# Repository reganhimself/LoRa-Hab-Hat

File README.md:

# Raspberry Zero LoRa HAB HAT
This is a Pi Hat designed to work with a Raspberry Pi. It was specifically designed to work with Raspberry Pi Zero and the mounting holes are lined up with Pi Zero in mind however it should still work with any other Pi. This board is designed to transform a Pi Zero into a tracker. On the board, you will find SMD pads to solder a LoRa module on to. The board supports the following modules: RFM95, RFM95, RFM97, RFM98. There is also an option of connecting a 6 pin GPS receiver to the board if needed as well. The breakout for Rasberry Pi provides not only pins but also pads. This gives you an ability to test with jumper wires and for use have a more permanent connection.

This board was made in collaboration with [Reganhimself](http://reganhimself.com). Tests and projects with this board will be on his forum.  

Here is a quick overview of the board:

# The top side

# Bottom side

# And here is the schematic for the board

# Our Board uses a standard Pi Zero pinout:

## BOM

| component  | Version  | Link  | Notes |
|---|---|---|---|
| Raspberry Pi Zero  | 1.3  | https://thepihut.com/products/raspberry-pi-zero |   |
| LoRa Module  | -  | https://store.uputronics.com/index.php?route=product/product&path=61&product_id=69  | (434MHz)  |
| uBLOX MAX-M8C  | -  | https://store.uputronics.com/index.php?route=product/product&path=60_64&product_id=72  | Chip Antenna |
| BME 280 Environmental Sensor   | -  | https://www.aliexpress.com/premium/bme280-sensor.html?d=y | optional |
| SMA Connector | - | - | - |
| Power Connector | - | - | - |

Gerber files, Eagle files and more can be found in the Documents Folder.

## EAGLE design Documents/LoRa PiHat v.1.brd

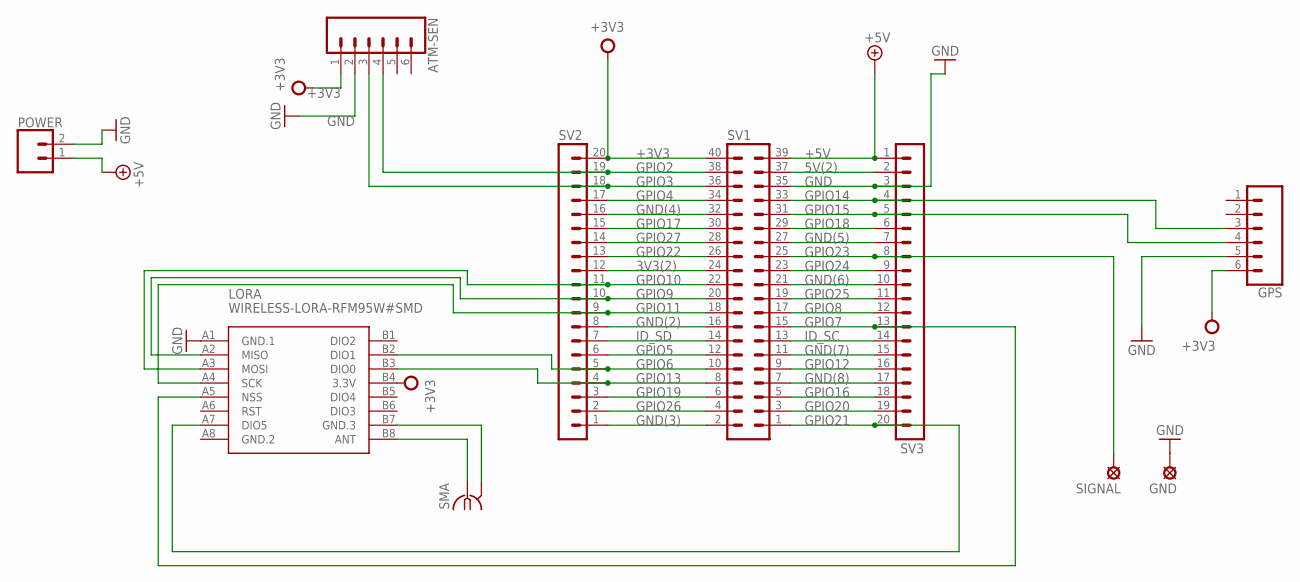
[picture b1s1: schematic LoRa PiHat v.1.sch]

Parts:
ATM-SEN: CONN_06NO_SILK_NO_POP; 1X06_NO_SILK
GND: LSP10
GPS: CONN_06NO_SILK_NO_POP; 1X06_NO_SILK
LORA: WIRELESS-LORA-RFM95W#SMD
POWER: CONN_02; 1X02
SIGNAL: LSP10
SMA: BU-SMA-V
SV1: MA20-2
SV2, SV3: MA20-1L

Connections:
3V3(2): SV1.24, SV2.12
5V(2): SV1.37, SV3.2
+3V3: ATM-SEN.1, GPS.6, LORA.B4 (3.3V), SV1.40, SV2.20
+5V: POWER.1, SV1.39, SV3.1
GND: ATM-SEN.2, GND.MP, GPS.5, LORA.A1 (GND.1), POWER.2, SV1.35, SV3.3
GND(2): SV1.16, SV2.8
GND(3): SV1.2, SV2.1
GND(4): SV1.32, SV2.16
GND(5): SV1.27, SV3.7
GND(6): SV1.21, SV3.10
GND(7): SV1.11, SV3.15
GND(8): SV1.7, SV3.17
GND.2: LORA.A8 (GND.2)
GPIO2: ATM-SEN.4, SV1.38, SV2.19
GPIO3: ATM-SEN.3, SV1.36, SV2.18
GPIO4: SV1.34, SV2.17
GPIO5: SV1.12, SV2.6
GPIO6: LORA.B2 (DIO1), SV1.10, SV2.5
GPIO7: LORA.A5 (NSS), SV1.15, SV3.13
GPIO8: SV1.17, SV3.12
GPIO9: LORA.A2 (MISO), SV1.20, SV2.10
GPIO10: LORA.A3 (MOSI), SV1.22, SV2.11
GPIO11: LORA.A4 (SCK), SV1.18, SV2.9
GPIO12: SV1.9, SV3.16
GPIO13: LORA.B3 (DIO0), SV1.8, SV2.4
GPIO14: GPS.3, SV1.33, SV3.4
GPIO15: GPS.4, SV1.31, SV3.5
GPIO16: SV1.5, SV3.18
GPIO17: SV1.30, SV2.15
GPIO18: SV1.29, SV3.6
GPIO19: SV1.6, SV2.3
GPIO20: SV1.3, SV3.19
GPIO21: LORA.A7 (DIO5), SV1.1, SV3.20
GPIO22: SV1.26, SV2.13
GPIO23: SIGNAL.MP, SV1.25, SV3.8
GPIO24: SV1.23, SV3.9
GPIO25: SV1.19, SV3.11
GPIO26: SV1.4, SV2.2
GPIO27: SV1.28, SV2.14
ID_SC: SV1.13, SV3.14
ID_SD: SV1.14, SV2.7
unnamed: LORA.B8 (ANT), SMA.1
unnamed: LORA.B7 (GND.3), SMA.2, SMA.3 (2), SMA.4 (2), SMA.5 (2)

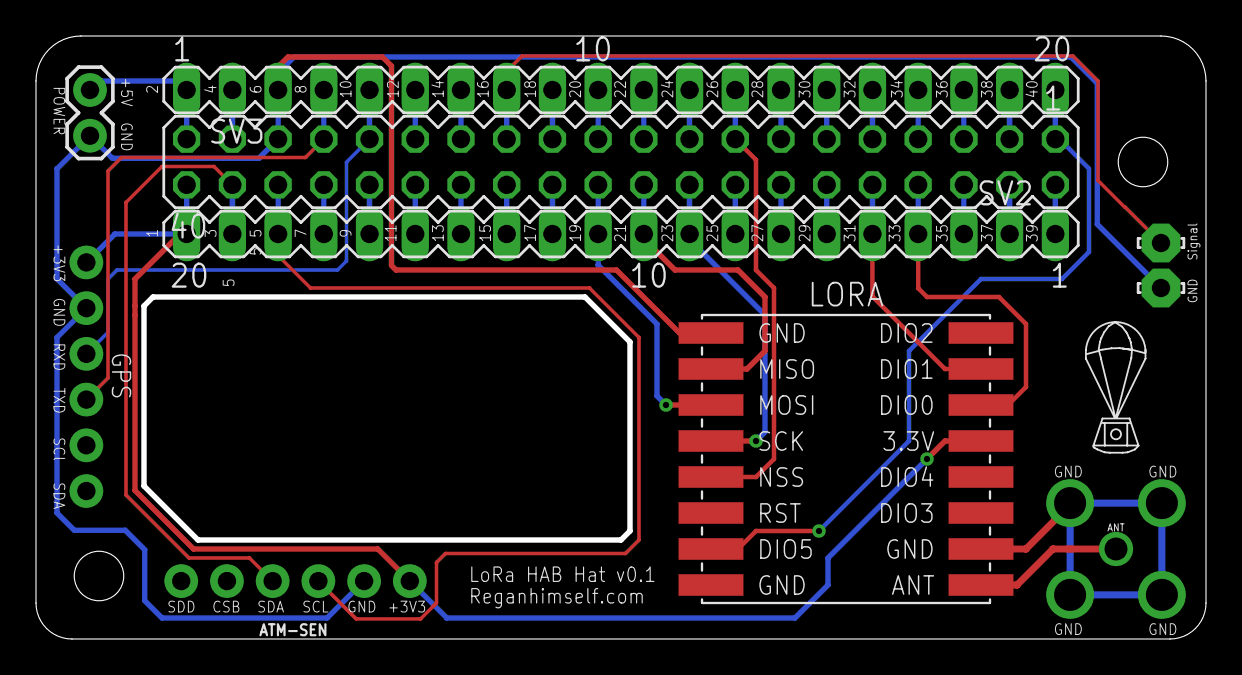
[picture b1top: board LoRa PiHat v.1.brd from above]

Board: 2 copper layers, 64.7 x 33.2 mm, 11 parts (1 on the bottom side), 42 nets.

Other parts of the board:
U$1: LOGO

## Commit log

2020-03-14 Create Documents
2020-03-15 Version 1.0 of the LoRa Pi Hat
2020-03-15 Folder for Utill files
2020-03-15 Pinout for Pi Zero
2020-03-15 More Info Added
2020-03-15 Spelling corrections
2020-03-15 Fixed links

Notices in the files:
parts and their libraries:
SparkFun-Connectors: Licensing: Creative Commons ShareAlike 4.0 International - https://creativecommons.org/licenses/by-sa/4.0
diy-modules: Released under the Creative Commons Attribution 4.0 International License: http://creativecommons.org/licenses/by/4.0
